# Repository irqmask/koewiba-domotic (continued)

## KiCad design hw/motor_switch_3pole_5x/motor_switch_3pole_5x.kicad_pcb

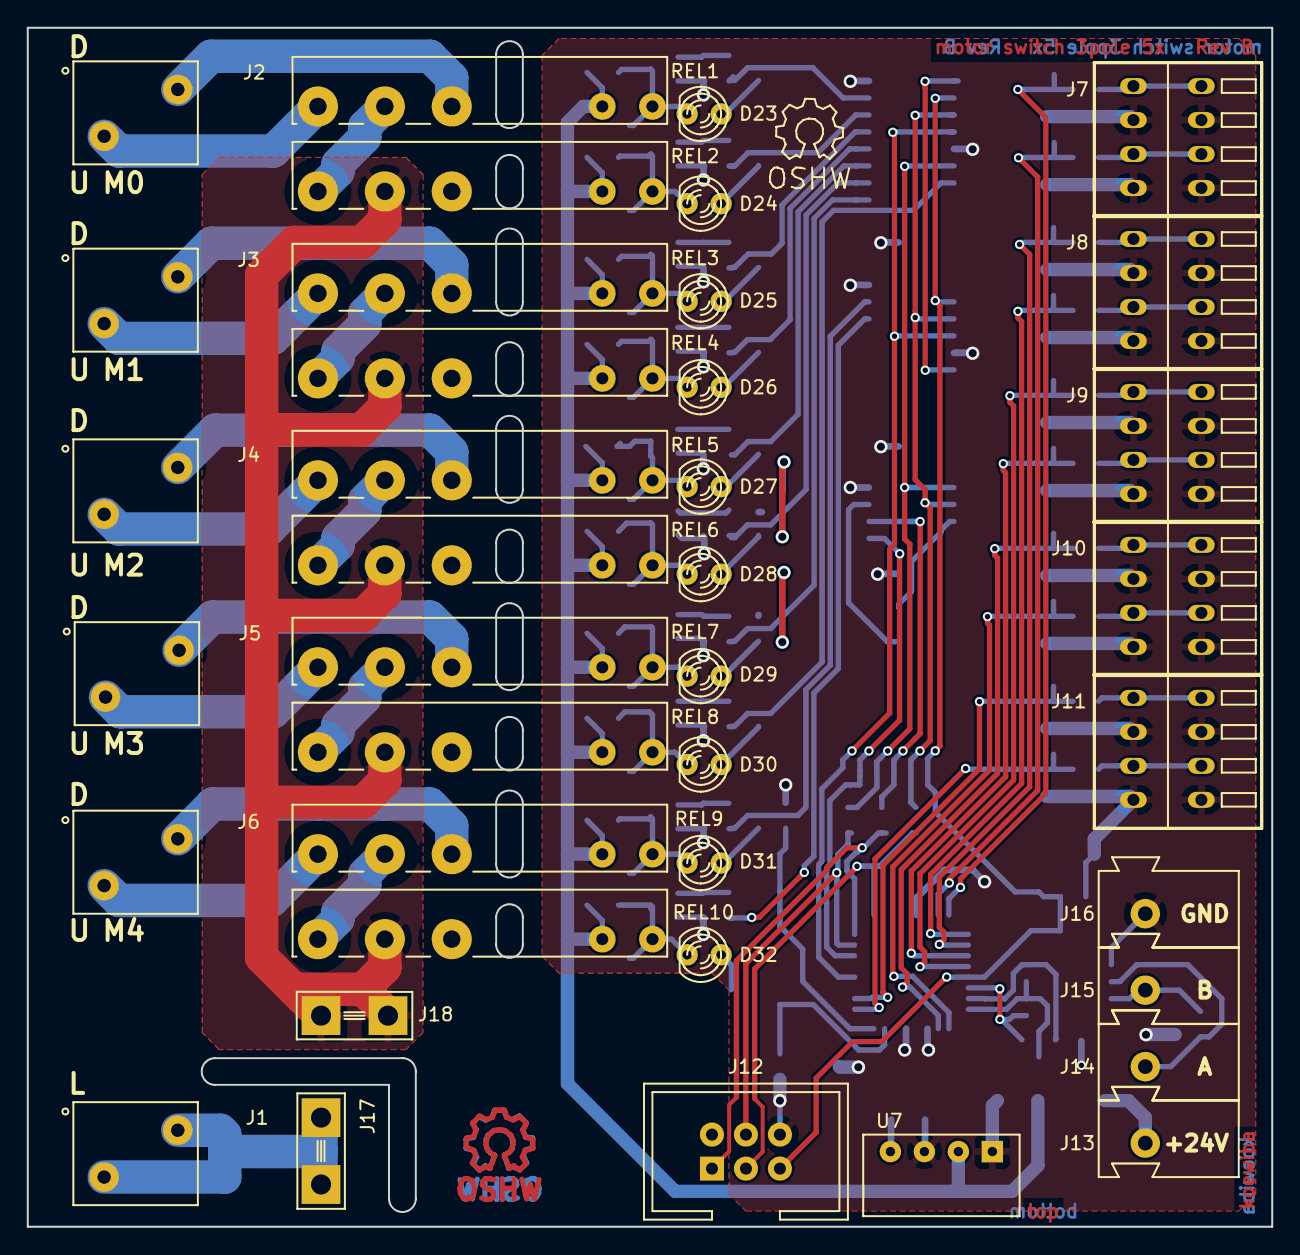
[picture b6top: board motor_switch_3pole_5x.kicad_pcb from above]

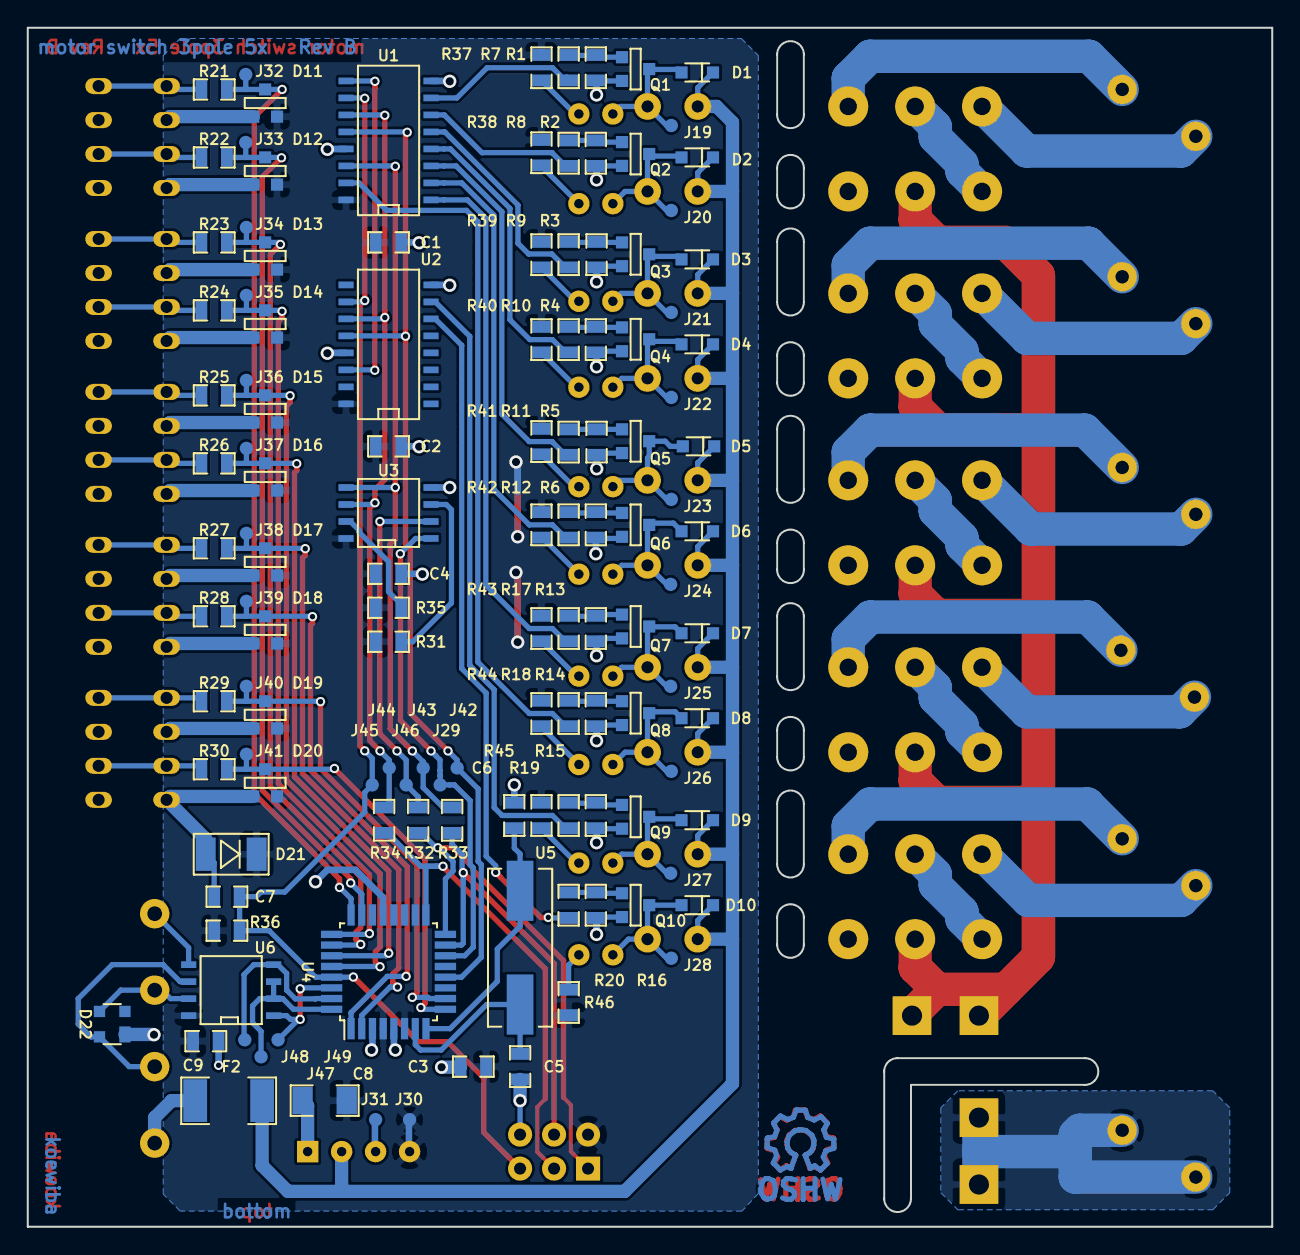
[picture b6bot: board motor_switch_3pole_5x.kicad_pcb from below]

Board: 2 copper layers, 93.0 x 89.6 mm, 167 parts (126 on the bottom side), 100 nets.

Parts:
C1, C2, C3, C4, C9: 100nF; C_0805
C5, C6: 18pF; C_0805
C7: 4,7nF; C_0805
C8: 100µF / 6V; C_1206
D1, D2, D3, D4, D5, D6, D7, D8, D9, D10: 1N4148; D_SOD323
D11, D12, D13, D14, D15, D16, D17, D18, D19, D20: BAT54S; SOT23-3
D21: ZD; D_MINIMELF
D22: SEMTECH SR05; D_SOT143
D23, D25, D27, D29, D31: yellow, 2,1V/2mA; LED_RM2.54mm_D3mm
D24, D26, D28, D30, D32: green, 2,2V/2mA; LED_RM2.54mm_D3mm
F2: FUSE; R_1812
J1: CONN_2X1; WAGO2081-1122
J2, J3, J4, J5, J6: WAGO 2081-1122; WAGO2081-1122
J7, J8, J9, J10, J11: WAGO 233-504; WAGO233-4
J12: CONN-ISP-6; HEADER_6
J13: WAGO 243-723; WAGO243
J14: WAGO 243-724; WAGO243
J15: WAGO 243-721; WAGO243
J16: WAGO 243-722; WAGO243
J17, J18: CONN_1; CONN1_6.35
J19: tp_output_motor_0_up; Testpoint_1mm
J20: tp_output_motor_on; Testpoint_1mm
J21: tp_output_motor_1_up; Testpoint_1mm
J22: tp_output_motor_1_on; Testpoint_1mm
J23: tp_output_motor_2_up; Testpoint_1mm
J24: tp_output_motor_2_on; Testpoint_1mm
J25: tp_output_motor_3_up; Testpoint_1mm
J26: tp_output_motor_3_on; Testpoint_1mm
J27: tp_output_motor_4_up; Testpoint_1mm
J28: tp_output_motor_4_on; Testpoint_1mm
J29: tp_cseep; Testpoint_1mm
J30: tp_vcc; Testpoint_1mm
J31: tp_gnd; Testpoint_1mm
J32: tp_output_button_0_up; Testpoint_1mm
J33: tp_output_button_0_down; Testpoint_1mm
J34: tp_output_button_1_up; Testpoint_1mm
J35: tp_output_button_1_down; Testpoint_1mm
J36: tp_output_button_2_up; Testpoint_1mm
J37: tp_output_button_2_down; Testpoint_1mm
J38: tp_output_button_3_up; Testpoint_1mm
J39: tp_output_button_3_down; Testpoint_1mm
J40: tp_output_button_4_up; Testpoint_1mm
J41: tp_output_button_4_down; Testpoint_1mm
J42: tp_output_latch; Testpoint_1mm
J43: tp_output_data; Testpoint_1mm
J44: tp_output_clock; Testpoint_1mm
J45: tp_output_reset; Testpoint_1mm
J46: tp_miso; Testpoint_1mm
J47: tp_txden; Testpoint_1mm
J48: tp_txd; Testpoint_1mm
J49: tp_rxd; Testpoint_1mm
LOGO1, LOGO2: OPEN_HARDWARE_1; Symbol_OSHW-Logo_Copper
LOGO4: Open Hardware; Symbol_OSHW-Logo_SilkScreen
Q1, Q2, Q3, Q4, Q5, Q6, Q7, Q8, Q9, Q10: BSS138; SOT23-3
R1, R2, R3, R4, R5, R6, R13, R14, R15, R16, R31, R35, R36: 10k; R_0805
R7, R8, R9, R10, R11, R12, R17, R18, R19, R20, R32, R33, R34: 100; R_0805
R21, R22, R23, R24, R25, R26, R27, R28, R29, R30: 4k7; R_0805
R37, R38, R39, R40, R41, R42, R43, R44, R45, R46: 1k5; R_0805
REL1, REL2, REL3, REL4, REL5, REL6, REL7, REL8, REL9, REL10: FINDER_34.51.7.024; finder_34.51_1xUM
U1, U2: 74HC595; SO16N
U3: 25LC256; SO8N
U4: ATMEGA328-TQFP32; TQFP-32_7x7mm_Pitch0.8mm
U5: 7,3728MHz; CRY_HC49_SMD
U6: MAX487ECSA; SO8N
U7: AM1S-2405; AM1S-XXXX_SIL4

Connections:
+5V: C1.1, C2.1, C3.1, C4.1, C8.1, C9.2, D11.2, D12.2, D13.2, D14.2, D15.2, D16.2, D17.2, D18.2, D19.2, D20.2, D21.2, J12.2, J30.1, R31.1, R35.1, R36.1, R37.2, R38.2, R39.2, R40.2, R41.2, R42.2, R43.2, R44.2, R45.2, R46.2, U1.16, U2.16, U3.8, U4.4, U4.6, U4.18, U6.8, U7.4
+24V: D1.2, D2.2, D3.2, D4.2, D5.2, D6.2, D7.2, D8.2, D9.2, D10.2, F2.1, REL1.2, REL2.2, REL3.2, REL4.2, REL5.2, REL6.2, REL7.2, REL8.2, REL9.2, REL10.2, U7.2
//button_0_down: D12.3, J33.1, R22.1, U4.23
//button_0_up: D11.3, J32.1, R21.1, U4.24
//button_1_down: D14.3, J35.1, R24.1, U4.25
//button_1_up: D13.3, J34.1, R23.1, U4.26
//button_2_down: D16.3, J37.1, R26.1, U4.27
//button_2_up: D15.3, J36.1, R25.1, U4.28
//button_3_down: D18.3, J39.1, R28.1, U4.1
//button_3_up: D17.3, J38.1, R27.1, U4.2
//button_4_down: D20.3, J41.1, R30.1, U4.9
//button_4_up: D19.3, J40.1, R29.1, U4.10
/Motor Relays/230V: J18.1, REL2.4, REL4.4, REL6.4, REL8.4, REL10.4
/Motor Relays/M0_230V_ON: REL1.4, REL2.5
/Motor Relays/M1_230V_ON: REL3.4, REL4.5
/Motor Relays/M2_230V_ON: REL5.4, REL6.5
/Motor Relays/M3_230V_ON: REL7.4, REL8.5
/Motor Relays/M4_230V_ON: REL9.4, REL10.5
/Motor Relays/MOTOR_0_230V_DOWN: J2.1, REL1.3
/Motor Relays/MOTOR_0_230V_UP: J2.2, REL1.5
/Motor Relays/MOTOR_1_230V_DOWN: J3.1, REL3.3
/Motor Relays/MOTOR_1_230V_UP: J3.2, REL3.5
/Motor Relays/MOTOR_2_230V_DOWN: J4.1, REL5.3
/Motor Relays/MOTOR_2_230V_UP: J4.2, REL5.5
/Motor Relays/MOTOR_3_230V_DOWN: J5.1, REL7.3
/Motor Relays/MOTOR_3_230V_UP: J5.2, REL7.5
/Motor Relays/MOTOR_4_230V_DOWN: J6.1, REL9.3
/Motor Relays/MOTOR_4_230V_UP: J6.2, REL9.5
/bus_atmega328_basic//CSEEP: J29.1, U3.1, U4.14
/bus_atmega328_basic/A: D22.4, J14.1, U6.6
/bus_atmega328_basic/B: D22.3, J15.1, U6.7
/bus_atmega328_basic/MISO: J46.1, R32.2, U3.2
/bus_atmega328_basic/PB3_MOSI: J12.4, R33.1, U4.15
/bus_atmega328_basic/PB4_MISO: J12.1, R32.1, U4.16
/bus_atmega328_basic/PB5_SCK: J12.3, R34.1, U4.17
/bus_atmega328_basic/RXD0: J49.1, U4.30, U6.1
/bus_atmega328_basic/TXD0: J48.1, U4.31, U6.4
/bus_atmega328_basic/TXD0EN: J47.1, U4.32, U6.2, U6.3
/motor_0_on: R8.2, U1.6
/motor_0_up: R7.2, U1.7
/motor_1_on: R10.2, U1.4
/motor_1_up: R9.2, U1.5
/motor_2_on: R12.2, U1.2
/motor_2_up: R11.2, U1.3
/motor_3_on: R18.2, U1.15
/motor_3_up: R17.2, U1.1
/motor_4_on: R20.2, U2.6
/motor_4_up: R19.2, U2.7
/output_clock: J44.1, R34.2, U1.11, U2.11, U3.6
/output_data: J43.1, R33.2, U1.14, U3.5
/output_latch: J42.1, U1.12, U2.12, U4.12
/output_reset: C7.1, J12.5, J45.1, R36.2, U1.10, U2.10, U4.29
GND: C1.2, C2.2, C3.2, C4.2, C5.2, C6.2, C7.2, C8.2, C9.1, D11.1, D12.1, D13.1, D14.1, D15.1, D16.1, D17.1, D18.1, D19.1, D20.1, D21.1, D22.1, J7.2, J7.4, J8.2, J8.4, J9.2, J9.4, J10.2, J10.4, J11.2, J11.4, J12.6, J16.1, J31.1, Q1.2, Q2.2, Q3.2, Q4.2, Q5.2, Q6.2, Q7.2, Q8.2, Q9.2, Q10.2, R1.2, R2.2, R3.2, R4.2, R5.2, R6.2, R13.2, R14.2, R15.2, R16.2, U1.8, U1.13, U2.8, U2.13, U3.4, U4.3, U4.5, U4.21, U6.5, U7.1, U7.3
unnamed: C5.1, U4.7, U5.1
unnamed: C6.1, U4.8, U5.2
unnamed: D1.1, D23.2, J19.1, Q1.3, REL1.1
unnamed: D2.1, D24.2, J20.1, Q2.3, REL2.1
unnamed: D10.1, D32.2, J28.1, Q10.3, REL10.1
unnamed: D23.1, R37.1
unnamed: D24.1, R38.1
unnamed: D25.1, R39.1
unnamed: D3.1, D25.2, J21.1, Q3.3, REL3.1
unnamed: D26.1, R40.1
unnamed: D4.1, D26.2, J22.1, Q4.3, REL4.1
unnamed: D27.1, R41.1
unnamed: D5.1, D27.2, J23.1, Q5.3, REL5.1
unnamed: D28.1, R42.1
unnamed: D6.1, D28.2, J24.1, Q6.3, REL6.1
unnamed: D29.1, R43.1
unnamed: D7.1, D29.2, J25.1, Q7.3, REL7.1
unnamed: D30.1, R44.1
unnamed: D8.1, D30.2, J26.1, Q8.3, REL8.1
unnamed: D31.1, R45.1
unnamed: D9.1, D31.2, J27.1, Q9.3, REL9.1
unnamed: D32.1, R46.1
unnamed: F2.2, J13.1
unnamed: J1.1, J1.2, J17.1
unnamed: J7.1, R21.2
unnamed: J7.3, R22.2
unnamed: J8.1, R23.2
unnamed: J8.3, R24.2
unnamed: J9.1, R25.2
unnamed: J9.3, R26.2
unnamed: J10.1, R27.2
unnamed: J10.3, R28.2
unnamed: J11.1, R29.2
unnamed: J11.3, R30.2
unnamed: Q1.1, R1.1, R7.1
unnamed: Q2.1, R2.1, R8.1
unnamed: Q3.1, R3.1, R9.1
unnamed: Q4.1, R4.1, R10.1
unnamed: Q5.1, R5.1, R11.1
unnamed: Q6.1, R6.1, R12.1
unnamed: Q7.1, R13.1, R17.1
unnamed: Q8.1, R14.1, R18.1
unnamed: Q9.1, R15.1, R19.1
unnamed: Q10.1, R16.1, R20.1
unnamed: R31.2, U3.3
unnamed: R35.2, U3.7
unnamed: U1.9, U2.14

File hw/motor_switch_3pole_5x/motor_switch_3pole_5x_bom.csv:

"Id";"Bezeichner";"Gehäuse";"Stückzahl";"Bezeichnung";"Anbieter und Ref";
1;"U1,U2";"SO16N";2;"74HC595";;;
2;"U3";"SO8N";1;"25LC256";;;
3;"U6";"SO8N";1;"MAX487ECSA";;;
4;"J13";"WAGO243";1;"WAGO 243-723";;;
5;"J14";"WAGO243";1;"WAGO 243-724";;;
6;"J15";"WAGO243";1;"WAGO 243-721";;;
7;"J16";"WAGO243";1;"WAGO 243-722";;;
8;"U7";"AM1S-XXXX_SIL4";1;"AM1S-2405";;;
9;"J12";"HEADER_6";1;"CONN-ISP-6";;;
10;"D23,D25,D27,D29,D31";"LED_RM2.54mm_D3mm";5;"yellow, 2,1V/2mA";;;
11;"D24,D26,D28,D30,D32";"LED_RM2.54mm_D3mm";5;"green, 2,2V/2mA";;;
12;"REL5,REL1,REL2,REL3,REL4,REL6,REL7,REL8,REL9,REL10";"finder_34.51_1xUM";10;"FINDER_34.51.7.024";;;
13;"J2,J3,J4,J5,J6";"WAGO2081-1122";5;"WAGO 2081-1122";;;
14;"R20,R7,R8,R9,R10,R11,R12,R17,R18,R19,R32,R33,R34";"R_0805";13;"100";;;
15;"R15,R1,R2,R3,R4,R5,R6,R13,R14,R16,R31,R35,R36";"R_0805";13;"10k";;;
16;"Q7,Q1,Q2,Q3,Q4,Q5,Q6,Q8,Q9,Q10";"SOT23-3";10;"BSS138";;;
17;"D11,D12,D13,D14,D15,D16,D17,D18,D19,D20";"SOT23-3";10;"BAT54S";;;
18;"D22";"D_SOT143";1;"SEMTECH SR05";;;
19;"F2";"R_1812";1;"FUSE";;;
20;"J1";"WAGO2081-1122";1;"CONN_2X1";;;
21;"J7,J8,J9,J10,J11";"WAGO233-4";5;"WAGO 233-504";;;
22;"LOGO1,LOGO2,LOGO3";"Symbol_OSHW-Logo_Copper";3;"OPEN_HARDWARE_1";;;
23;"LOGO4";"Symbol_OSHW-Logo_SilkScreen";1;"Open Hardware";;;
24;"C1,C2,C3,C4,C9";"C_0805";5;"100nF";;;
25;"C5,C6";"C_0805";2;"18pF";;;
26;"C7";"C_0805";1;"4,7nF";;;
27;"C8";"C_1206";1;"100µF / 6V";;;
28;"D1,D2,D3,D4,D5,D6,D7,D8,D9,D10";"D_SOD323";10;"1N4148";;;
29;"D21";"D_MINIMELF";1;"ZD";;;
30;"R21,R22,R23,R24,R25,R26,R27,R28,R29,R30";"R_0805";10;"4k7";;;
31;"U5";"CRY_HC49_SMD";1;"7,3728MHz";;;
32;"U4";"TQFP-44_10x10mm_Pitch0.8mm";1;"ATMEGA328-TQFP32";;;
33;"J17,J18";"CONN1_6.35";2;"CONN_1";;;
34;"R37,R38,R39,R40,R41,R42,R43,R44,R45,R46";"R_0805";10;"1k5";;;
35;"J19";"Testpoint_1mm";1;"tp_output_motor_0_up";;;
36;"J20";"Testpoint_1mm";1;"tp_output_motor_on";;;
37;"J21";"Testpoint_1mm";1;"tp_output_motor_1_up";;;
38;"J22";"Testpoint_1mm";1;"tp_output_motor_1_on";;;
39;"J23";"Testpoint_1mm";1;"tp_output_motor_2_up";;;
40;"J24";"Testpoint_1mm";1;"tp_output_motor_2_on";;;
41;"J25";"Testpoint_1mm";1;"tp_output_motor_3_up";;;
42;"J26";"Testpoint_1mm";1;"tp_output_motor_3_on";;;
43;"J27";"Testpoint_1mm";1;"tp_output_motor_4_up";;;
44;"J28";"Testpoint_1mm";1;"tp_output_motor_4_on";;;
45;"J29";"Testpoint_1mm";1;"tp_cseep";;;
46;"J30";"Testpoint_1mm";1;"tp_vcc";;;
47;"J31";"Testpoint_1mm";1;"tp_gnd";;;
48;"J32";"Testpoint_1mm";1;"tp_output_button_0_up";;;
49;"J33";"Testpoint_1mm";1;"tp_output_button_0_down";;;
50;"J34";"Testpoint_1mm";1;"tp_output_button_1_up";;;
51;"J35";"Testpoint_1mm";1;"tp_output_button_1_down";;;
52;"J36";"Testpoint_1mm";1;"tp_output_button_2_up";;;
53;"J37";"Testpoint_1mm";1;"tp_output_button_2_down";;;
54;"J38";"Testpoint_1mm";1;"tp_output_button_3_up";;;
55;"J39";"Testpoint_1mm";1;"tp_output_button_3_down";;;
56;"J40";"Testpoint_1mm";1;"tp_output_button_4_up";;;
57;"J41";"Testpoint_1mm";1;"tp_output_button_4_down";;;
58;"J42";"Testpoint_1mm";1;"tp_output_latch";;;
59;"J43";"Testpoint_1mm";1;"tp_output_data";;;
60;"J44";"Testpoint_1mm";1;"tp_output_clock";;;
61;"J45";"Testpoint_1mm";1;"tp_output_reset";;;
62;"J46";"Testpoint_1mm";1;"tp_miso";;;
63;"J47";"Testpoint_1mm";1;"tp_txden";;;
64;"J48";"Testpoint_1mm";1;"tp_txd";;;
65;"J49";"Testpoint_1mm";1;"tp_rxd";;;

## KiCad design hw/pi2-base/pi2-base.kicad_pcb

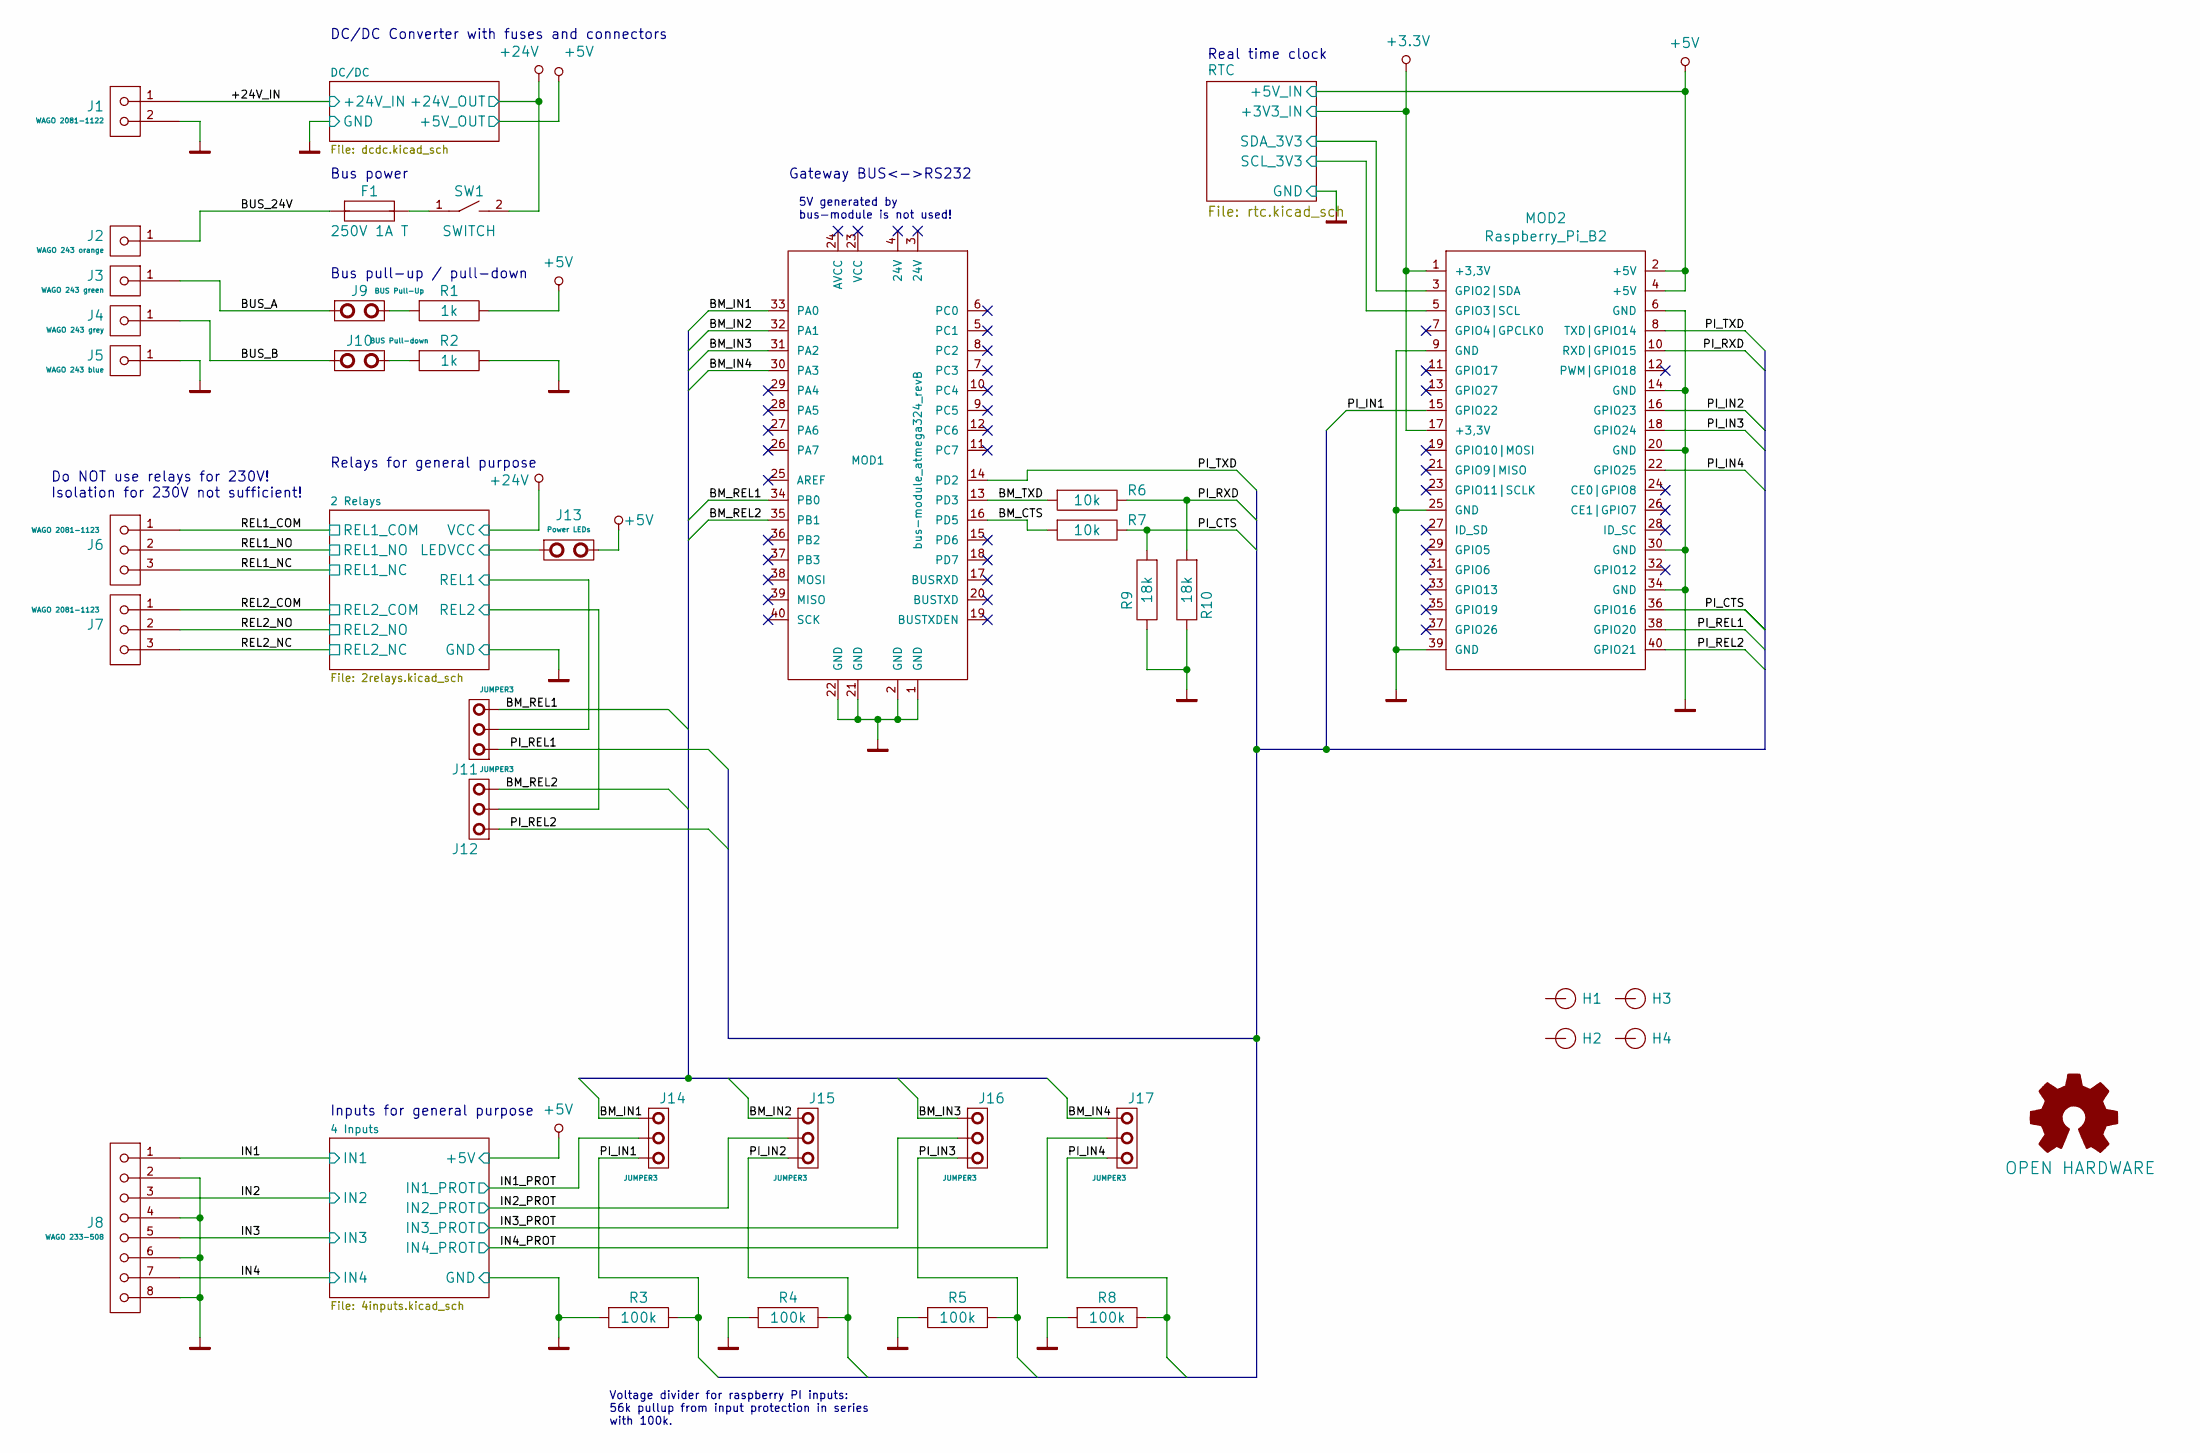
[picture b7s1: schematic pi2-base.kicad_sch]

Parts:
F1: 250V 1A T; FUSE5-20
H1, H2, H3, H4: HOLE; HOLE_3.5mm
J1: WAGO 2081-1122; WAGO_2081-1122
J2: WAGO 243 orange; WAGO_243
J3: WAGO 243 green; WAGO_243
J4: WAGO 243 grey; WAGO_243
J5: WAGO 243 blue; WAGO_243
J6, J7: WAGO 2081-1123; WAGO_2081-1123
J8: WAGO 233-508; WAGO_233-8
J9: BUS Pull-Up; HEADER_2x1
J10: BUS Pull-down; HEADER_2x1
J11, J12, J14, J15, J16, J17: JUMPER3; HEADER_3x1
J13: Power LEDs; HEADER_2x1
LOGO1: OPEN HARDWARE; Symbol_OSHW-Logo_Copper
MOD1: bus-module_atmega324_revB
MOD2: Raspberry_Pi_B2; raspberry_pi2
R1, R2: 1k; R_0805
R3, R4, R5, R8: 100k; R_0805
R6, R7: 10k; R_0805
R9, R10: 18k; R_0805
SW1: SWITCH; PCB_CON2

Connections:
+3.3V: MOD2.1 (+3,3V), MOD2.17 (+3,3V); also elsewhere on the board
+5V: J13.2, MOD2.2 (+5V), MOD2.4 (+5V), R1.2; also elsewhere on the board
+24V: SW1.2; also elsewhere on the board
/2 Relays/LEDVCC: J13.1; also elsewhere on the board
/2 Relays/REL1: J11.2; also elsewhere on the board
/2 Relays/REL2: J12.2; also elsewhere on the board
/+24V_IN: J1.1; also elsewhere on the board
/BM_CTS: MOD1.16 (PD5), R7.1
/BM_IN1: J14.1, MOD1.33 (PA0)
/BM_IN2: J15.1, MOD1.32 (PA1)
/BM_IN3: J16.1, MOD1.31 (PA2)
/BM_IN4: J17.1, MOD1.30 (PA3)
/BM_REL1: J11.3, MOD1.34 (PB0)
/BM_REL2: J12.3, MOD1.35 (PB1)
/BM_TXD: MOD1.13 (PD3), R6.1
/BUS_24V: F1.1, J2.1
/BUS_A: J3.1, J9.1
/BUS_B: J4.1, J10.1
/IN1: J8.1; also elsewhere on the board
/IN1_PROT: J14.2; also elsewhere on the board
/IN2: J8.3; also elsewhere on the board
/IN2_PROT: J15.2; also elsewhere on the board
/IN3: J8.5; also elsewhere on the board
/IN3_PROT: J16.2; also elsewhere on the board
/IN4: J8.7; also elsewhere on the board
/IN4_PROT: J17.2; also elsewhere on the board
/PI_CTS: MOD2.36 (GPIO16), R7.2, R9.1
/PI_IN1: J14.3, MOD2.15 (GPIO22), R3.2
/PI_IN2: J15.3, MOD2.16 (GPIO23), R4.2
/PI_IN3: J16.3, MOD2.18 (GPIO24), R5.2
/PI_IN4: J17.3, MOD2.22 (GPIO25), R8.2
/PI_REL1: J11.1, MOD2.38 (GPIO20)
/PI_REL2: J12.1, MOD2.40 (GPIO21)
/PI_RXD: MOD2.10 (RXD|GPIO15), R6.2, R10.1
/PI_TXD: MOD1.14 (PD2), MOD2.8 (TXD|GPIO14)
/REL1_COM: J6.1; also elsewhere on the board
/REL1_NC: J6.3; also elsewhere on the board
/REL1_NO: J6.2; also elsewhere on the board
/REL2_COM: J7.1; also elsewhere on the board
/REL2_NC: J7.3; also elsewhere on the board
/REL2_NO: J7.2; also elsewhere on the board
/RTC/SCL_3V3: MOD2.5 (GPIO3|SCL); also elsewhere on the board
/RTC/SDA_3V3: MOD2.3 (GPIO2|SDA); also elsewhere on the board
GND: J1.2, J5.1, J8.2, J8.4, J8.6, J8.8, MOD1.1 (GND), MOD1.2 (GND), MOD1.21 (GND), MOD1.22 (GND), MOD2.6 (GND), MOD2.9 (GND), MOD2.14 (GND), MOD2.20 (GND), MOD2.25 (GND), MOD2.30 (GND), MOD2.34 (GND), MOD2.39 (GND), R2.2, R3.1, R4.1, R5.1, R8.1, R9.2, R10.2; also elsewhere on the board
unnamed: F1.2, SW1.1
unnamed: J9.2, R1.1
unnamed: J10.2, R2.1

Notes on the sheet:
Bus pull-up / pull-down
Bus power
Do NOT use relays for 230V! Isolation for 230V not sufficient!
Voltage divider for raspberry PI inputs: 56k pullup from input protection in series with 100k.
Gateway BUS<->RS232
5V generated by bus-module is not used!
Real time clock
Relays for general purpose
DC/DC Converter with fuses and connectors
Inputs for general purpose

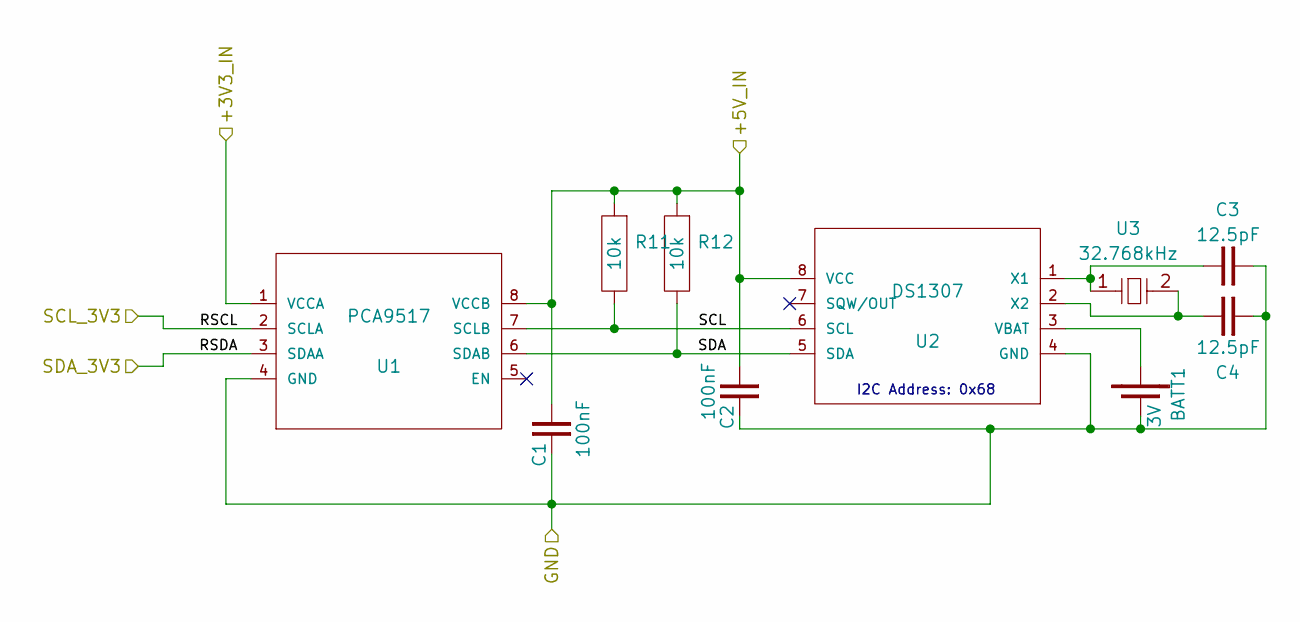
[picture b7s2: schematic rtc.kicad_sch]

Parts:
BATT1: 3V; CR2032H
C1, C2: 100nF; C_0805
C3, C4: 12.5pF; C_0805
R11, R12: 10k; R_0805
U1: PCA9517; SO8E
U2: DS1307; SO8E
U3: 32.768kHz; CRY_MS1V-7_SMD

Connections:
+3.3V: U1.1 (VCCA); also elsewhere on the board
+5V: C1.1, C2.1, R11.1, R12.1, U1.8 (VCCB), U2.8 (VCC); also elsewhere on the board
/RTC/SCL: R11.2, U1.7 (SCLB), U2.6 (SCL)
/RTC/SCL_3V3: U1.2 (SCLA); also elsewhere on the board
/RTC/SDA: R12.2, U1.6 (SDAB), U2.5 (SDA)
/RTC/SDA_3V3: U1.3 (SDAA); also elsewhere on the board
GND: BATT1.2 (-), C1.2, C2.2, C3.1, C4.1, U1.4 (GND), U2.4 (GND); also elsewhere on the board
unnamed: BATT1.1 (+), U2.3 (VBAT)
unnamed: C3.2, U2.1 (X1), U3.1
unnamed: C4.2, U2.2 (X2), U3.2

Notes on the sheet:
I2C Address: 0x68

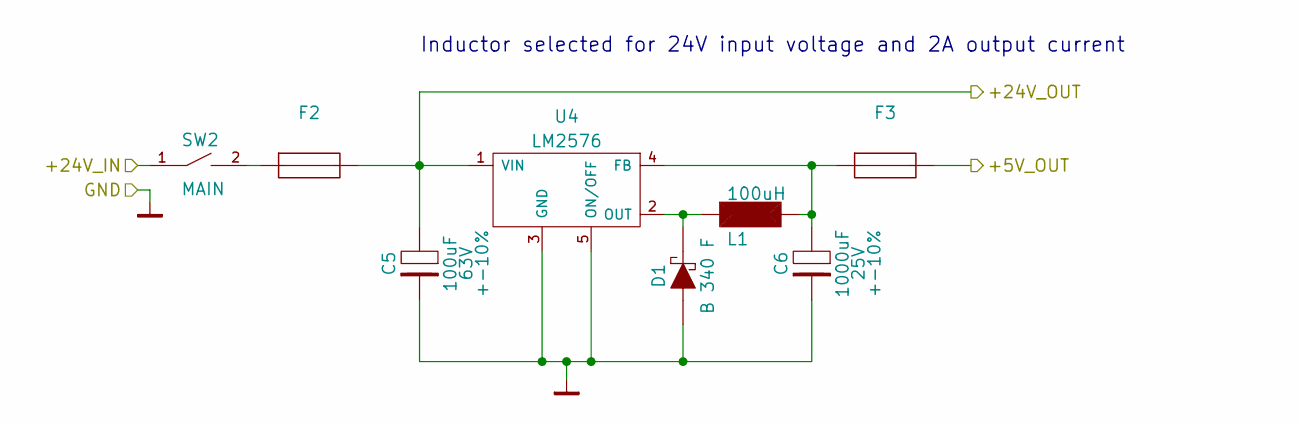
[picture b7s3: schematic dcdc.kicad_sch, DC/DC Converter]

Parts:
C5: 100uF; CP_RM5.08mm_D10.5mm; Voltage 63V
C6: 1000uF; CP_RM5.08mm_D13.5mm; Voltage 25V
D1: B 340 F; D_SMC
F2, F3: (no value)
L1: 100uH; L_PISR
SW2: MAIN; PCB_CON2
U4: LM2576; TO263_5

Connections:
+5V: F3.2; also elsewhere on the board
+24V: C5.1, F2.2, U4.1 (VIN); also elsewhere on the board
/+24V_IN: SW2.1; also elsewhere on the board
GND: C5.2, C6.2, D1.1 (A), U4.3 (GND), U4.5 (ON/OFF); also elsewhere on the board
unnamed: C6.1, F3.1, L1.2, U4.4 (FB)
unnamed: D1.2 (C), L1.1, U4.2 (OUT)
unnamed: F2.1, SW2.2

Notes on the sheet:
Inductor selected for 24V input voltage and 2A output current

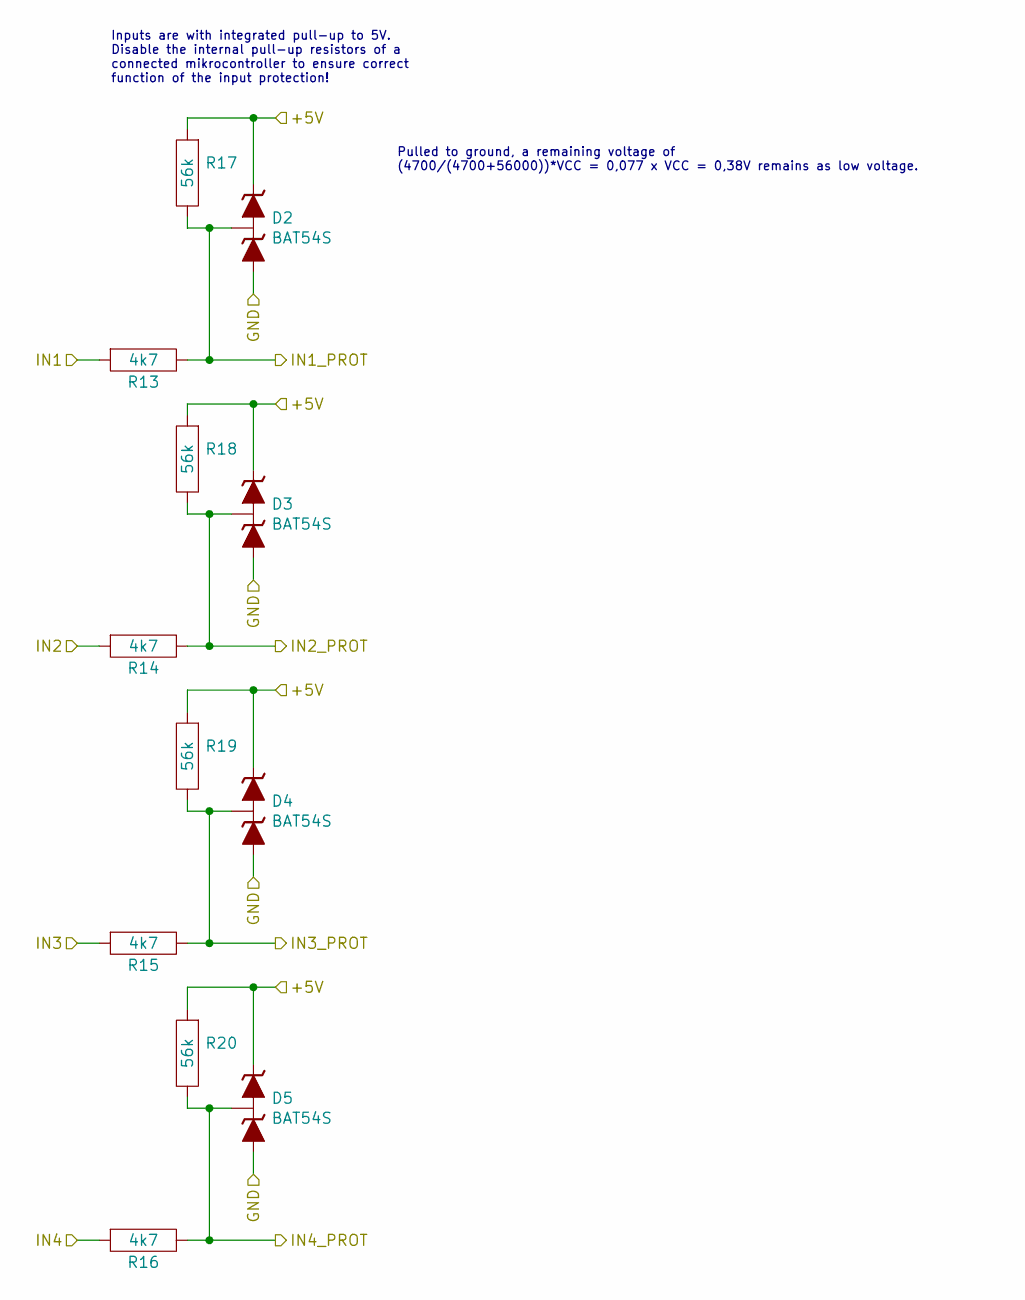
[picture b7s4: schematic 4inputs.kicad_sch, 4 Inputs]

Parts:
D2, D3, D4, D5: BAT54S; SOT23-3
R13, R14, R15, R16: 4k7; R_0805
R17, R18, R19, R20: 56k; R_0805

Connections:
+5V: D2.2, D3.2, D4.2, D5.2, R17.1, R18.1, R19.1, R20.1; also elsewhere on the board
/IN1: R13.1; also elsewhere on the board
/IN1_PROT: D2.3, R13.2, R17.2; also elsewhere on the board
/IN2: R14.1; also elsewhere on the board
/IN2_PROT: D3.3, R14.2, R18.2; also elsewhere on the board
/IN3: R15.1; also elsewhere on the board
/IN3_PROT: D4.3, R15.2, R19.2; also elsewhere on the board
/IN4: R16.1; also elsewhere on the board
/IN4_PROT: D5.3, R16.2, R20.2; also elsewhere on the board
GND: D2.1, D3.1, D4.1, D5.1; also elsewhere on the board

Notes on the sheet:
Inputs are with integrated pull-up to 5V. Disable the internal pull-up resistors of a connected mikrocontroller to ensure correct function of the input protection!
Pulled to ground, a remaining voltage of (4700/(4700+56000))*VCC = 0,077 x VCC = 0,38V remains as low voltage.

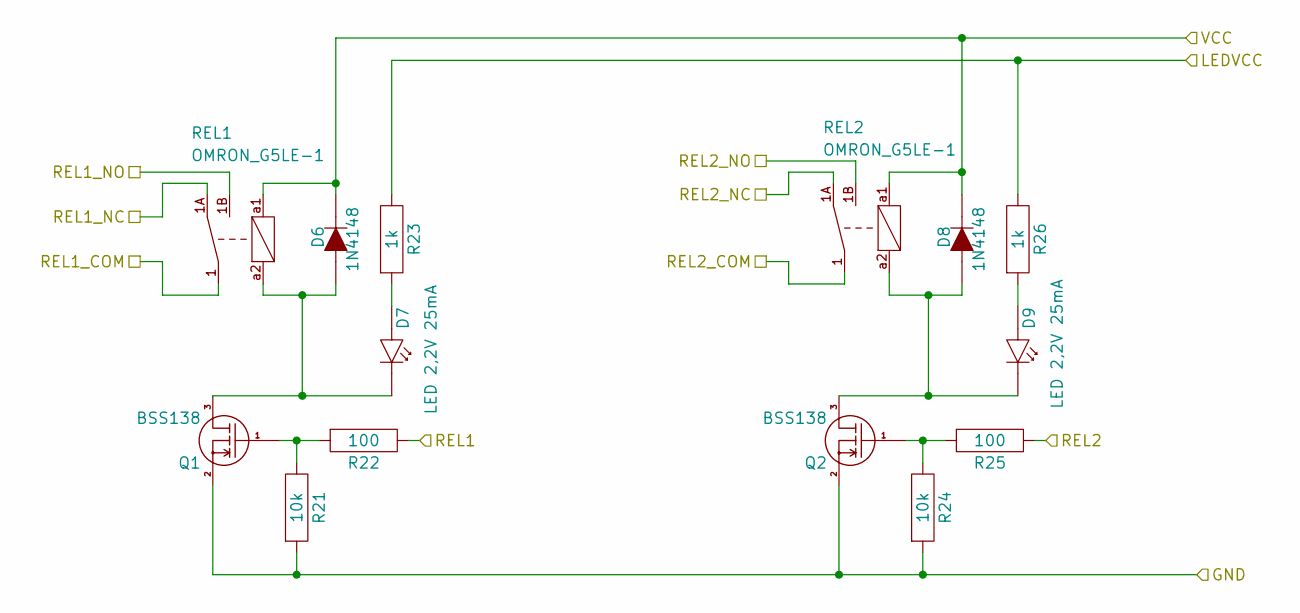
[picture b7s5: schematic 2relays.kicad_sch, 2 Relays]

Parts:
D6, D8: 1N4148; D_MINIMELF
D7, D9: LED 2,2V 25mA; LED_RM2.54mm_D3mm
Q1, Q2: BSS138; SOT23-3
R21, R24: 10k; R_0805
R22, R25: 100; R_0805
R23, R26: 1k; R_0805
REL1, REL2: OMRON_G5LE-1

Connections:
+24V: D6.2 (C), D8.2 (C), REL1.a1 (+), REL2.a1 (+); also elsewhere on the board
/2 Relays/LEDVCC: R23.2, R26.2; also elsewhere on the board
/2 Relays/REL1: R22.2; also elsewhere on the board
/2 Relays/REL2: R25.2; also elsewhere on the board
/REL1_COM: REL1.1; also elsewhere on the board
/REL1_NC: REL1.1A; also elsewhere on the board
/REL1_NO: REL1.1B; also elsewhere on the board
/REL2_COM: REL2.1; also elsewhere on the board
/REL2_NC: REL2.1A; also elsewhere on the board
/REL2_NO: REL2.1B; also elsewhere on the board
GND: Q1.2 (S), Q2.2 (S), R21.1, R24.1; also elsewhere on the board
unnamed: D6.1 (A), D7.2 (C), Q1.3 (D), REL1.a2 (-)
unnamed: D7.1 (A), R23.1
unnamed: D8.1 (A), D9.2 (C), Q2.3 (D), REL2.a2 (-)
unnamed: D9.1 (A), R26.1
unnamed: Q1.1 (G), R21.2, R22.1
unnamed: Q2.1 (G), R24.2, R25.1
